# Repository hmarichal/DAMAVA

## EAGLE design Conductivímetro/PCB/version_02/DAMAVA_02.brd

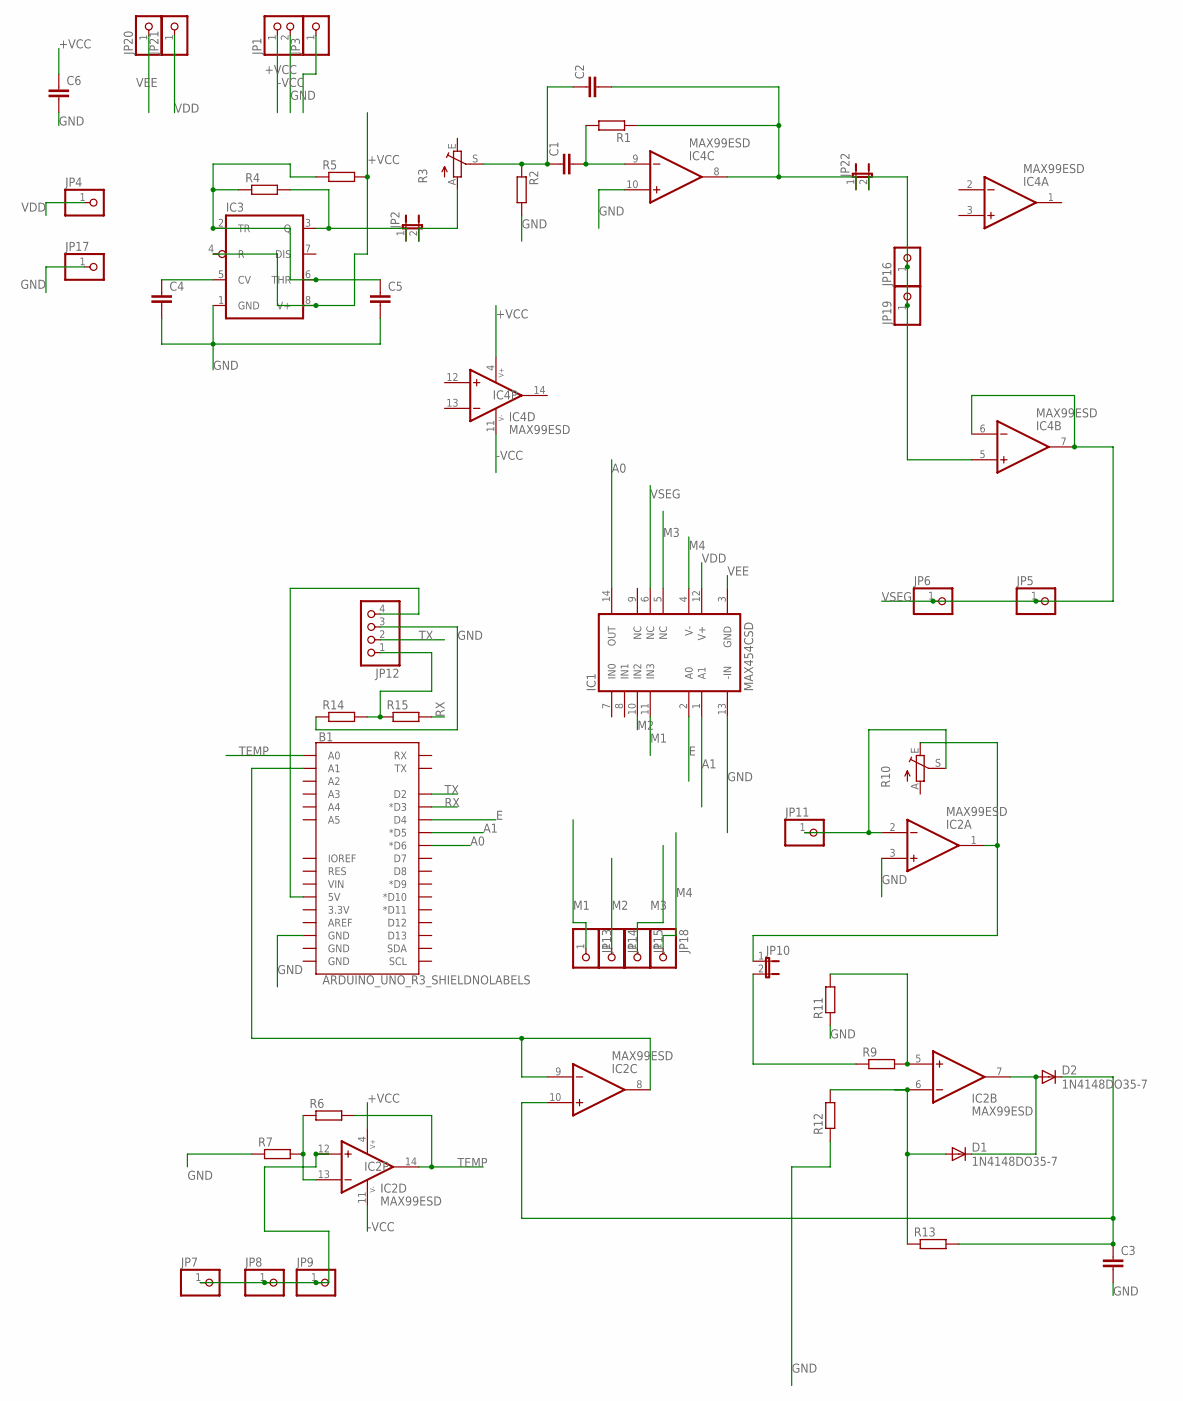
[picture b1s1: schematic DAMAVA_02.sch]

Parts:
B1: ARDUINO_UNO_R3_SHIELDNOLABELS; UNO_R3_SHIELD_NOLABELS
C1, C2, C4, C5, C6: C-EU050-024X044; C050-024X044
C3: C5/2.5; C5B2.5
D1, D2: 1N4148DO35-7; DO35-7
IC1: MAX454CSD; SO14
IC2, IC4: MAX99ESD; SO14
IC3: TLC555DIL08-2; DIL08-2
JP1: PINHD-1X2; 1X02
JP2, JP10, JP22: JP1E; JP1
JP3, JP4, JP5, JP6, JP7, JP8, JP9, JP11, JP13, JP14, JP15, JP16, JP17, JP18, JP19, JP20, JP21: PINHD-1X1; 1X01
JP12: PINHD-1X4; 1X04
R1, R2, R4, R5, R6, R7, R9, R11, R12, R13, R14, R15: R-EU_0204/5; 0204/5
R3, R10: TRIM_EU-B90P; SP19L

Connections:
+VCC: C6.1, IC2.4 (V+), IC3.4 (R), IC3.8 (V+), IC4.4 (V+), JP1.1, R5.2
-VCC: IC2.11 (V-), IC4.11 (V-), JP1.2
A0: B1.D6 (*D6), IC1.14 (OUT)
A1: B1.D5 (*D5), IC1.1 (A1)
E: B1.D4, IC1.2 (A0)
GND: B1.GND@2 (GND), C3.2, C4.2, C5.2, C6.2, IC1.13 (-IN), IC2.3 (+IN), IC3.1 (GND), IC4.10 (+IN), JP3.1, JP12.3, JP17.1, R2.2, R7.1, R11.1, R12.1, R14.1
M1: IC1.11 (IN3), JP13.1
M2: IC1.10 (IN2), JP14.1
M3: IC1.5 (NC), JP15.1
M4: IC1.4 (V-), JP18.1
unnamed: C1.2, IC4.9 (-IN), R1.2
unnamed: C1.1, C2.1, R2.1, R3.S
unnamed: JP2.2, R3.A
unnamed: C5.1, IC3.2 (TR), IC3.6 (THR), R4.1, R5.1
unnamed: IC3.3 (Q), JP2.1, R4.2
unnamed: C3.1, D2.C, IC2.10 (+IN), R13.2
unnamed: IC2.13 (-IN), R6.1, R7.2
unnamed: IC4.5 (+IN), JP16.1, JP19.1, JP22.2
unnamed: IC2.12 (+IN), JP7.1, JP8.1, JP9.1
unnamed: IC2.2 (-IN), JP11.1, R10.S
unnamed: B1.A1, IC2.8 (OUT), IC2.9 (-IN)
unnamed: IC2.1 (OUT), JP10.1, R10.E
unnamed: IC2.5 (+IN), R9.2, R11.2
unnamed: JP10.2, R9.1
unnamed: JP12.1, R14.2, R15.1
unnamed: C2.2, IC4.8 (OUT), JP22.1, R1.1
unnamed: D1.A, IC2.6 (-IN), R12.2, R13.1
unnamed: D1.C, D2.A, IC2.7 (OUT)
unnamed: B1.5V, JP12.4
unnamed: C4.1, IC3.5 (CV)
RX: B1.D3 (*D3), R15.2
TEMP: B1.A0, IC2.14 (OUT), R6.2
TX: B1.D2, JP12.2
VDD: IC1.12 (V+), JP4.1, JP21.1
VEE: IC1.3 (GND), JP20.1
VSEG: IC1.6 (NC), IC4.6 (-IN), IC4.7 (OUT), JP5.1, JP6.1

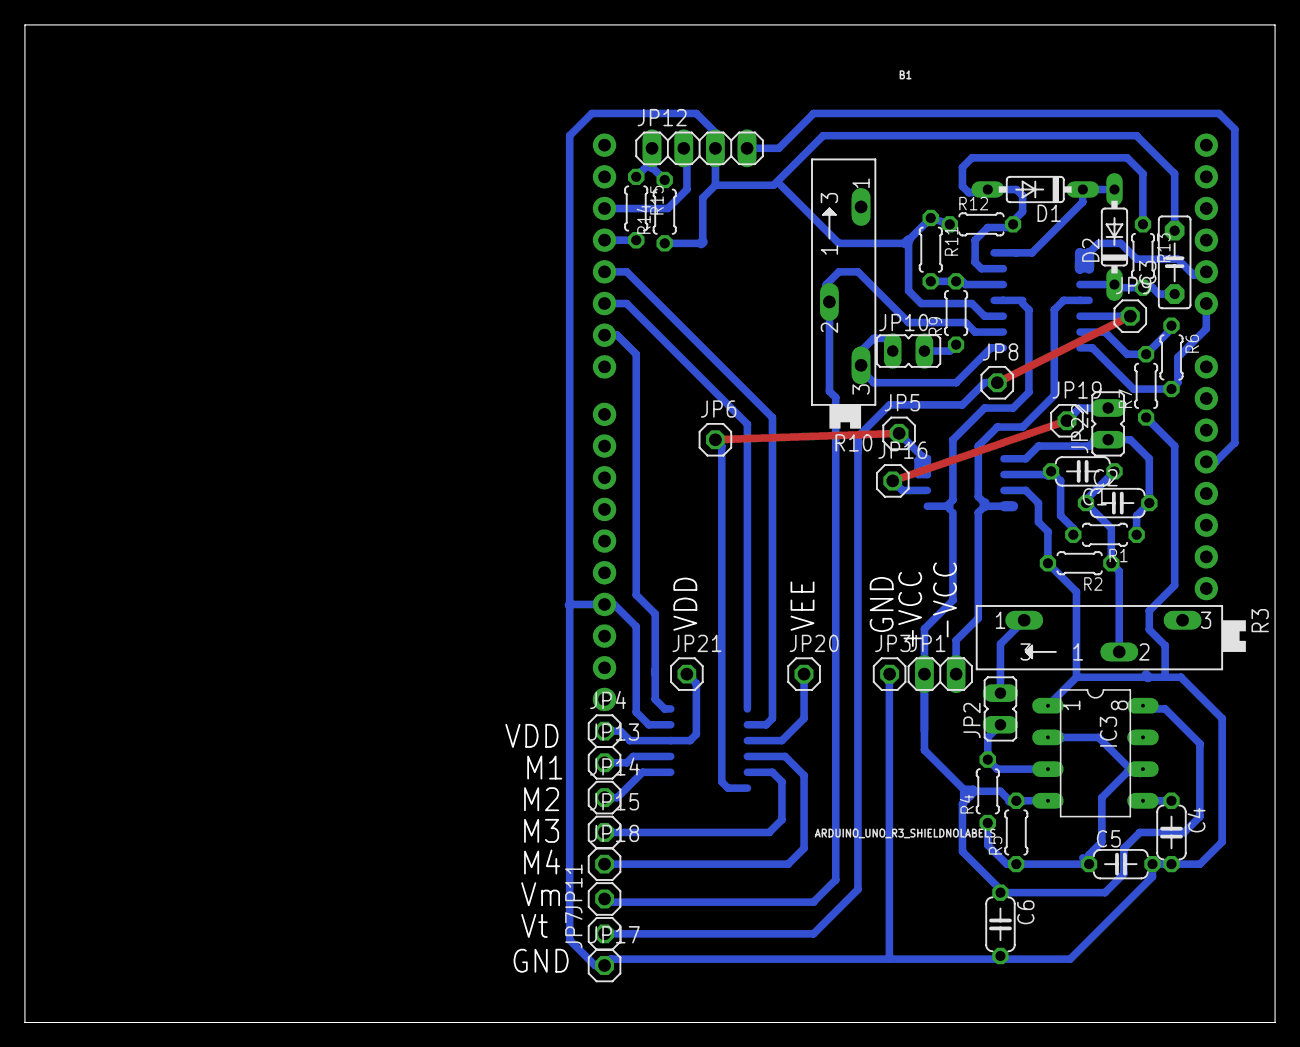
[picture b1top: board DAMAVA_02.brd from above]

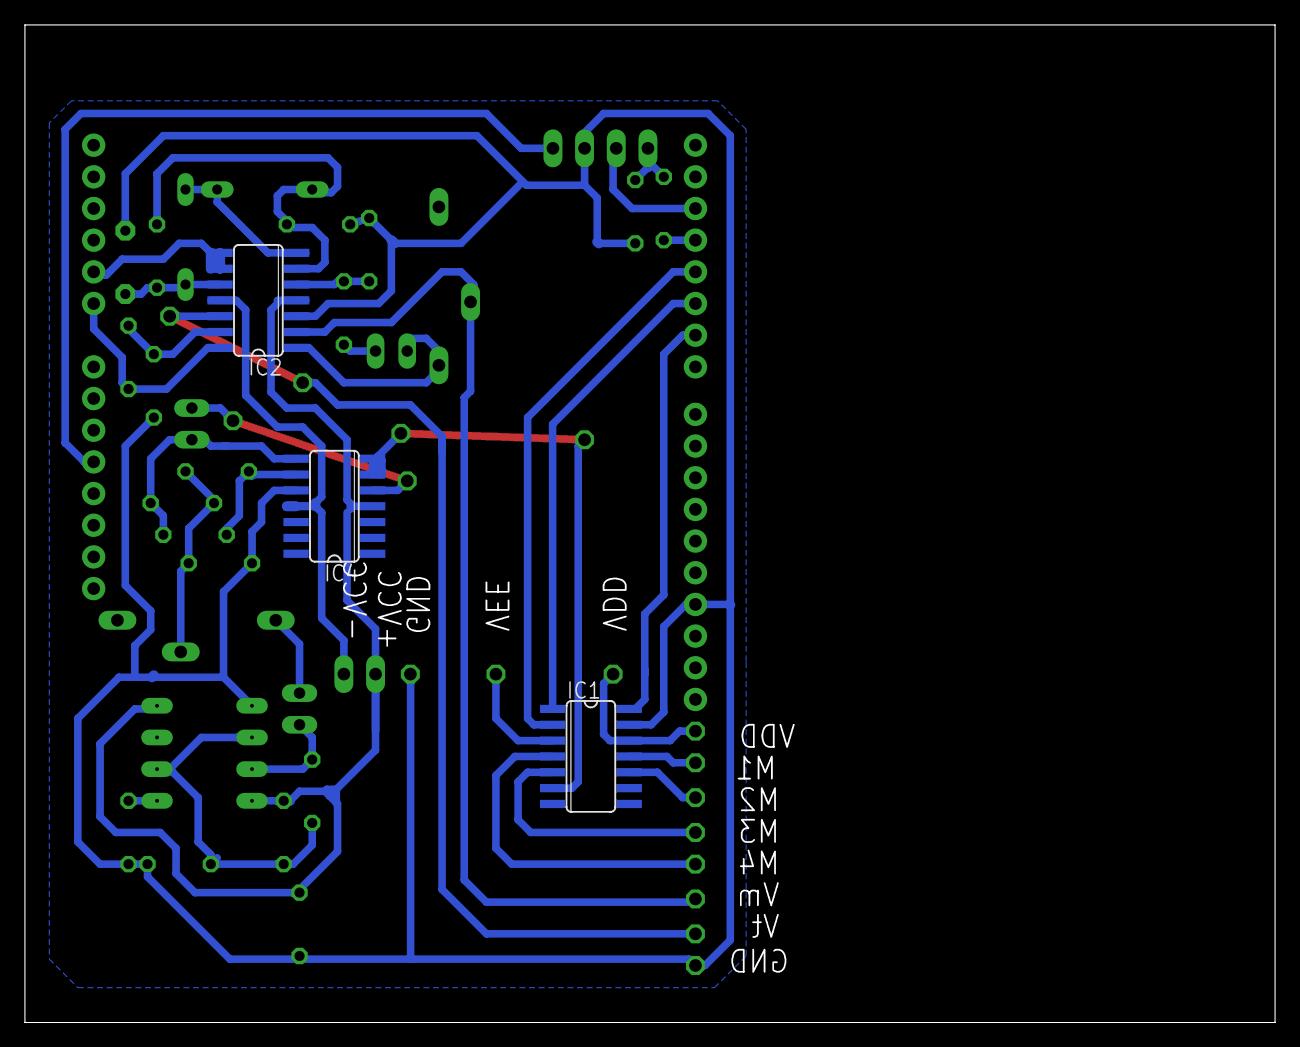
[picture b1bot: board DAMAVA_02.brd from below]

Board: 2 copper layers, 100.3 x 80.0 mm, 49 parts (3 on the bottom side), 36 nets.

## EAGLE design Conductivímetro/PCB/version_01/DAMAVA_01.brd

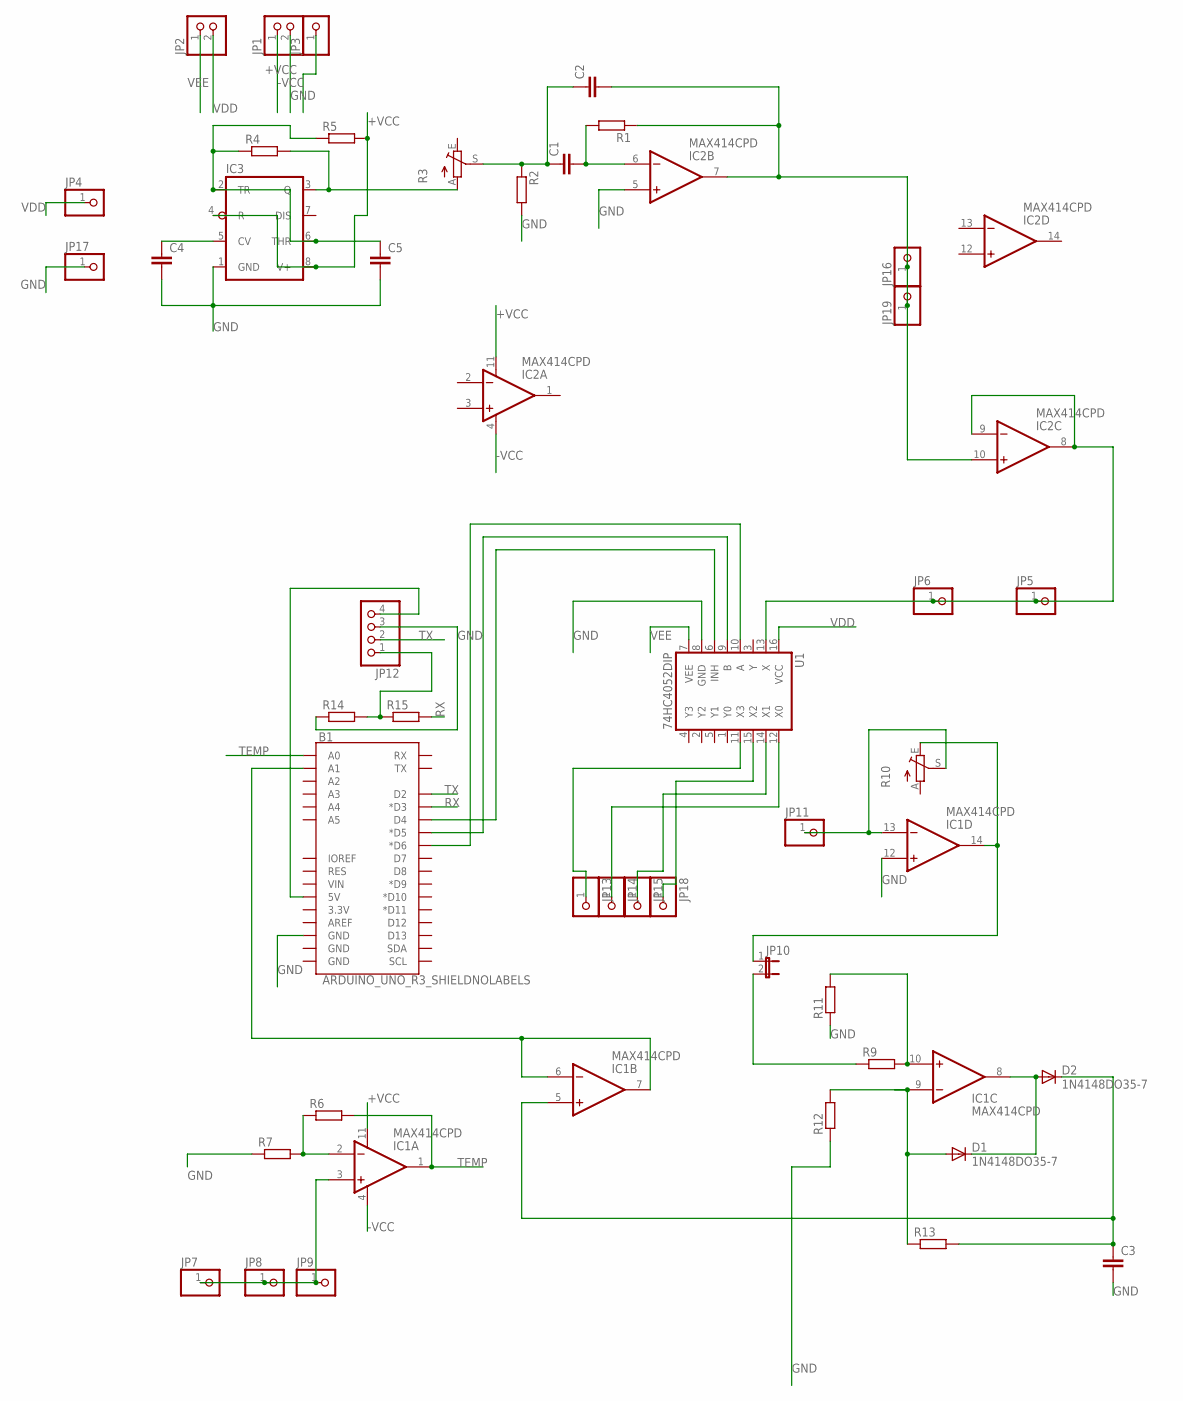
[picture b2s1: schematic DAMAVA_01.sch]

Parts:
B1: ARDUINO_UNO_R3_SHIELDNOLABELS; UNO_R3_SHIELD_NOLABELS
C1, C2, C4, C5: C-EU050-024X044; C050-024X044
C3: C5/2.5; C5B2.5
D1, D2: 1N4148DO35-7; DO35-7
IC1, IC2: MAX414CPD; DIL14
IC3: TLC555DIL08-2; DIL08-2
JP1, JP2: PINHD-1X2; 1X02
JP3, JP4, JP5, JP6, JP7, JP8, JP9, JP11, JP13, JP14, JP15, JP16, JP17, JP18, JP19: PINHD-1X1; 1X01
JP10: JP1E; JP1
JP12: PINHD-1X4; 1X04
R1, R2, R4, R5, R6, R7, R9, R11, R12, R13, R14, R15: R-EU_0204/5; 0204/5
R3, R10: TRIM_EU-B90P; SP19L
U1: 74HC4052DIP; DIL16

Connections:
+VCC: IC1.11 (V-), IC2.11 (V-), IC3.4 (R), IC3.8 (V+), JP1.1, R5.2
-VCC: IC1.4 (V+), IC2.4 (V+), JP1.2
GND: B1.GND@2 (GND), C3.2, C4.2, C5.2, IC1.12 (+IN), IC2.5 (+IN), IC3.1 (GND), JP3.1, JP12.3, JP17.1, R2.2, R7.1, R11.1, R12.1, R14.1, U1.8 (GND)
unnamed: C1.2, IC2.6 (-IN), R1.2
unnamed: C1.1, C2.1, R2.1, R3.S
unnamed: B1.D6 (*D6), U1.10 (A)
unnamed: C5.1, IC3.2 (TR), IC3.6 (THR), R4.1, R5.1
unnamed: IC3.3 (Q), R3.A, R4.2
unnamed: C3.1, D2.C, IC1.5 (+IN), R13.2
unnamed: IC1.2 (-IN), R6.1, R7.2
unnamed: B1.D5 (*D5), U1.9 (B)
unnamed: IC1.3 (+IN), JP7.1, JP8.1, JP9.1
unnamed: B1.D4, U1.6 (INH)
unnamed: JP14.1, U1.12 (X0)
unnamed: JP15.1, U1.14 (X1)
unnamed: JP13.1, U1.11 (X3)
unnamed: IC1.13 (-IN), JP11.1, R10.S
unnamed: JP18.1, U1.15 (X2)
unnamed: B1.A1, IC1.6 (-IN), IC1.7 (OUT)
unnamed: IC2.8 (OUT), IC2.9 (-IN), JP5.1, JP6.1, U1.13 (X)
unnamed: IC1.14 (OUT), JP10.1, R10.E
unnamed: IC1.10 (+IN), R9.2, R11.2
unnamed: JP10.2, R9.1
unnamed: JP12.1, R14.2, R15.1
unnamed: C2.2, IC2.7 (OUT), IC2.10 (+IN), JP16.1, JP19.1, R1.1
unnamed: D1.A, IC1.9 (-IN), R12.2, R13.1
unnamed: D1.C, D2.A, IC1.8 (OUT)
unnamed: B1.5V, JP12.4
unnamed: C4.1, IC3.5 (CV)
RX: B1.D3 (*D3), R15.2
TEMP: B1.A0, IC1.1 (OUT), R6.2
TX: B1.D2, JP12.2
VDD: JP2.2, JP4.1, U1.16 (VCC)
VEE: JP2.1, U1.7 (VEE)

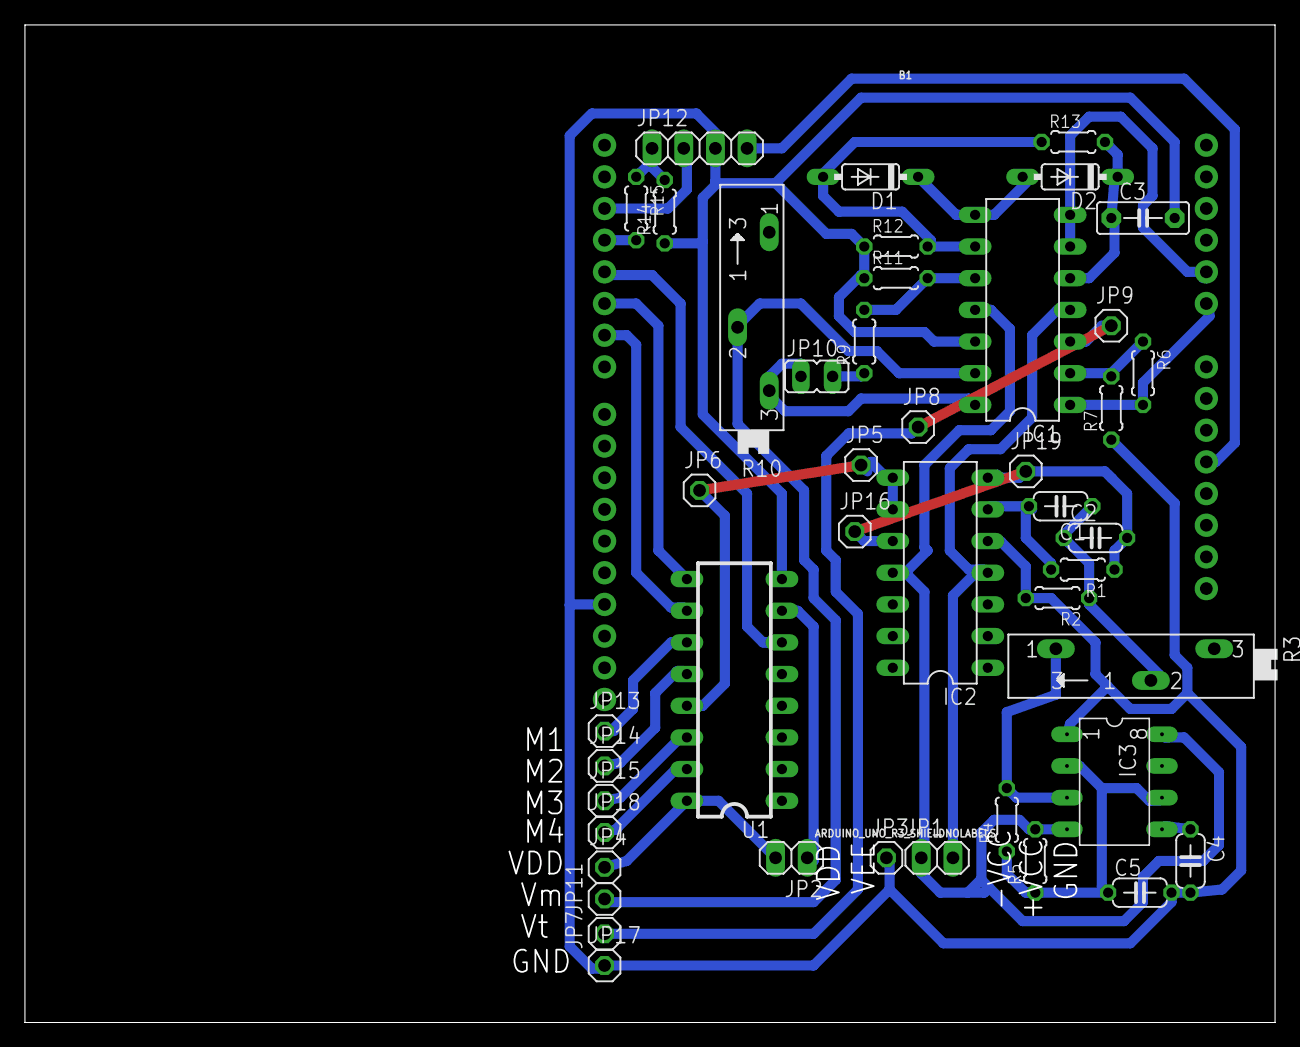
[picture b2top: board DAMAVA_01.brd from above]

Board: 2 copper layers, 100.3 x 80.0 mm, 45 parts (0 on the bottom side), 34 nets.

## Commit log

2017-08-30 SW UM
2017-08-30 cambios
2017-08-31 main conjunto modulo comandos
2017-08-31 compilando1
2017-09-01 entregables
2017-09-01 agregado mux
2017-09-02 probando hm10
2017-09-18 versiones
2017-09-29 respaldo drive
2017-09-29 bitacora
2017-09-29 actualizar
2017-09-29 prueba
2017-09-29 cambio nombre carpeta
2017-09-29 actualizacion pcb
2017-10-03 correcciones main y modulo mux
2017-10-03 2octubre
2017-10-06 modelado
2017-10-12 software
2017-10-12 modulo commands testeado correctamente
2017-10-15 fin sw arduino
2017-10-20 actualización sw UM
2017-10-21 software UM documentado
2017-10-23 actualizado sw
2017-11-01 swLecpro
2017-11-02 modificaciones sw lecpro um
2017-11-29 testing sw
2017-12-03 actualizacion
2018-01-07 ultima actualizacion
2018-01-13 paralelo
2018-01-14 paralelisacion-pipe-servidorMovil
2018-01-15 agregado servidor celular
2018-01-15 sw arduino terminado
2018-01-15 cambio de nombre simulacionUM
2018-02-03 backup
2018-04-29 cambiso
2018-05-03 se agrego clase bluetoothRFcomm
2018-05-06 sw limpio
2018-05-07 version semi final
2018-05-09 cambios2
2018-05-09 cambios para que anda rpi
2018-05-15 archivo de medidas
2018-05-15 todo

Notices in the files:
parts and their libraries:
SparkFun-Boards: Licensing: Creative Commons ShareAlike 4.0 International - https://creativecommons.org/licenses/by-sa/4.0
SparkFun-AnalogIC: Licensing: CC v3.0 Share-Alike You are welcome to use this library for commercial purposes.
